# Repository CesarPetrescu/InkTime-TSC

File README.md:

# InkTime Smartwatch

**Student:** Cesar Petrescu  
**Group:** 334CD  
**Course:** Testarea Sistemelor de Calcul - Proiect 2026

## Project Overview

This repository contains the complete hardware design for the InkTime smartwatch project.

The watch is built around the Nordic nRF52840 and combines BLE connectivity, an e-paper display, IMU-based motion sensing, USB-C charging, a fuel gauge, a haptic motor driver, and a buck-boost power stage that generates a stable 3.3 V rail from the battery / charger system rail.

## Block Diagram

## Renders and Mechanical Integration

## Repository Outputs

| Directory | File | Purpose |
|---|---|---|
| `Hardware` | `project-tsc.sch` | Fusion 360 / EAGLE schematic source |
| `Hardware` | `project-tsc.brd` | Fusion 360 / EAGLE PCB source |
| `Hardware` | `schema.pdf` | Schematic print-out for review |
| `Manufacturing` | `gerbers.zip` | Gerber manufacturing archive |
| `Manufacturing` | `InkTime.bom` | Assembly Bill of Materials exported from the board |
| `Manufacturing` | `project-tsc.cpl` | Pick and Place / component placement file |
| `Mechanical` | `Exploded.step` | Complete device STEP model in exploded view |
| `Mechanical` | `Closed.step` | Complete device STEP model in closed/assembled view |

## Design BOM Summary

The assembly-ready BOM exported from the board is included in `Manufacturing/InkTime.bom`. The table below repeats the relevant manufacturing data from that file so the design can be reviewed directly from this README.

### Main fitted parts

| Ref | MPN / Value | Qty | Package / footprint | LCSC / procurement | Function | Datasheet / reference |
|---|---|---:|---|---|---|---|
| U1 | NRF52840-QIAA-R | 1 | AQFN50P700X700X85 HS-74N | [C190794](https://www.lcsc.com/product-detail/C190794.html) | Main MCU, BLE radio, USB device | [Nordic product specification](https://docs-be.nordicsemi.com/bundle/nRF52840_PS_v1.8/raw/resource/enus/nRF52840_PS_v1.8.pdf) |
| IC1 | BQ25180YBGR | 1 | BGA8C40P2X4 100X155X50 | [C3682423](https://www.lcsc.com/product-detail/C3682423.html) | Li-ion charger, power path, ship mode | [TI datasheet](https://www.ti.com/lit/ds/symlink/bq25180.pdf) |
| IC9 | RT6160AWSC | 1 | BGA15C40P3X5 140X230X60 | [C7065276](https://www.lcsc.com/product-detail/C7065276.html) | 3 A buck-boost regulator for 3V3 | [Richtek datasheet](https://www.richtek.com/assets/product_file/RT6160A/DS6160A-05.pdf) |
| U2 | MAX17048G+T10 | 1 | SON50P200X200X80-9N | [C89903](https://www.lcsc.com/product-detail/C89903.html) | Battery fuel gauge | [Analog Devices datasheet](https://www.analog.com/media/en/technical-documentation/data-sheets/max17048-max17049.pdf) |
| IC3 | BMA421 | 1 | BMA423 / LGA-12 | [C5242966](https://www.lcsc.com/product-detail/C5242966.html) | Low-power accelerometer / step counter | [Bosch datasheet](https://www.bosch-sensortec.com/media/boschsensortec/downloads/datasheets/bst-bma421-ds000.pdf) |
| IC2 | DRV2605YZFR | 1 | BGA9C50P3X3 144X144X62 | [C81079](https://www.lcsc.com/product-detail/C81079.html) | Haptic driver for ERM/LRA motor | [TI datasheet](https://www.ti.com/lit/ds/symlink/drv2605.pdf) |
| ANT1 | 2450AT18B100E | 1 | ANTC3216X140N | [C155086](https://www.lcsc.com/product-detail/C155086.html) | 2.4 GHz chip antenna | [Johanson datasheet](https://www.johansontechnology.com/datasheets/2450AT18B100/2450AT18B100.pdf) |
| J4 | KH-TYPE-C-16P | 1 | KINGHELM KH-TYPE-C-16P | [C2765186](https://www.lcsc.com/product-detail/C2765186.html) | USB-C receptacle for VBUS and USB 2.0 data | [JLCPCB part page](https://jlcpcb.com/partdetail/KH-TYPE-C-16P/C2765186) |
| D3 | USBLC6-2SC6Y | 1 | SOT95P280X145-6N | [C7519](https://www.lcsc.com/product-detail/C7519.html) | USB ESD protection | [ST datasheet](https://www.st.com/resource/en/datasheet/usblc6-2.pdf) |
| J2 | 503480-2400 | 1 | 503480-2400 5034802400 | [C132354](https://www.lcsc.com/product-detail/C132354.html) | 24-pin 0.5 mm FPC connector for e-paper | [Molex product page](https://www.molex.com/en-us/products/part-detail/5034802400) |
| J1 | TC2030-IDC | 1 DNP | TC2030IDC | Tag-Connect / DNP footprint | SWD programming and debug footprint | [Mechanical drawing](https://www.digikey.com/en/htmldatasheets/production/2094274/0/0/1/tc2030-idc.html) |
| SW_UP, SW_ENT, SW_DN | EVP-AKE31A | 3 | EVP-AKE31A PAN | [C220990](https://www.lcsc.com/product-detail/C220990.html) | Side tactile buttons | [Panasonic product page](https://industry.panasonic.com/global/en/products/control/switch/light-touch/number/evpake31a) |
| D2, D4, D5 | MBR0530T1G | 3 | SOD3716X135N | [C14156](https://www.lcsc.com/product-detail/C14156.html) | E-paper boost Schottky diodes | [onsemi datasheet](https://www.onsemi.com/pdf/datasheet/mbr0530t1-d.pdf) |
| Q1 | DMG2305UX-7 | 1 | SOT-23 | [C7418](https://www.lcsc.com/product-detail/C7418.html) | P-MOSFET display power gate | [Diodes Inc datasheet](https://www.diodes.com/assets/Datasheets/DMG2305UX.pdf) |
| Q3 | SI1308EDL-T1-GE3 | 1 | SOT-323 | [C146997](https://www.lcsc.com/product-detail/C146997.html) | N-MOSFET display driver switch | [Vishay datasheet](https://www.vishay.com/docs/63399/si1308edl.pdf) |
| X1 | X322532MSB4SI, 32 MHz | 1 | XTAL 2016 N | [C9002](https://www.lcsc.com/product-detail/C9002.html) | Main high-frequency crystal | [LCSC reference](https://www.lcsc.com/product-detail/C9002.html) |
| X2 | X322532768KHZ, 32.768 kHz | 1 | XTAL 3215 N | [C32346](https://www.lcsc.com/product-detail/C32346.html) | Low-frequency RTC crystal | [LCSC reference](https://www.lcsc.com/product-detail/C32346.html) |
| Battery | LP502030, 3.7 V, 250 mAh | 1 | Custom 3D model | [TME product page](https://www.tme.eu/ro/details/accu-lp502030_cl/acumulatori/cellevia-batteries/l502030/) | Main LiPo energy source | [AKYGA LP502030 datasheet](https://www.tme.eu/Document/b9e12bf26ad0ba929a22ab5d58f022cd/AKY0106.pdf) |
| Display | Waveshare 1.54 inch e-paper, 200x200 | 1 | Custom 3D model + J2 FPC | [TME product page](https://www.tme.eu/en/details/wsh-12561/e-paper/waveshare/12561/) | Main user display | [Specification PDF](https://www.tme.eu/Document/0ca57a8ffbcd57b5bca53252eb9d6ec3/WSH-12561.pdf) |
| Motor | FIT0774 | 1 | Custom 3D model / direct wiring | [TME product page](https://www.tme.eu/ro/details/df-fit0774/motoare-dc/dfrobot/fit0774/) | Vibration motor for haptics | [DFRobot product page](https://www.dfrobot.com/product-2297.html) |

### Inductors and passive fitted parts

| Ref | Value / MPN | Qty | Footprint | LCSC / procurement | Notes |
|---|---|---:|---|---|---|
| L1 | LQG15HS3N9S02D, 3.9 nH | 1 | RESC0402 L | [C1581](https://www.lcsc.com/product-detail/C1581.html) | RF matching network |
| L2 | SDFL1005S100KTF, 10 uH | 1 | RESC0402 L | [C1046](https://www.lcsc.com/product-detail/C1046.html) | E-paper power stage |
| L3 | LQG15HS15NJ02D, 15 nH | 1 | RESC0402 L | [C1588](https://www.lcsc.com/product-detail/C1588.html) | RF matching network |
| L5 | 68 uH generic chip inductor | 1 | RESC0402 L | Custom / verify before order | E-paper boost inductor |
| L7 | FTC252012SR47MBCA, 0.47 uH | 1 | INDC2016X100N | [C5832368](https://www.lcsc.com/product-detail/C5832368.html) | RT6160 buck-boost inductor |
| C1-ED-DR | 10 uF, CL05A106MQ5NUNC | 1 | RESC0402 N | [C19702](https://www.lcsc.com/product-detail/C19702.html) | E-paper bulk capacitor |
| C1, C2, C17, C18 | 12 pF, CL03C120JA3NNNC | 4 | RESC0201 L | [C1551](https://www.lcsc.com/product-detail/C1551.html) | Crystal load capacitors |
| C2-EP-DR, C6, C20, C21 | 4.7 uF, CL05A475KQ5NQNC | 4 | RESC0402 N | [C19666](https://www.lcsc.com/product-detail/C19666.html) | Power decoupling / display rail |
| C3, C4 | 1 pF, CL03C010CA3GNNC | 2 | RESC0201 N | [C1546](https://www.lcsc.com/product-detail/C1546.html) | RF matching capacitors |
| C5, C7, C8, C12, C19, C23, C27, C34, C42 | 100 nF / 0.1 uF, CL03A104KA3NNNC | 9 | 0201 variants | [C1525](https://www.lcsc.com/product-detail/C1525.html) | Local decoupling capacitors |
| C9 | 820 pF, CL03B821KO3NNNC | 1 | RESC0201 N | [C3014407](https://www.lcsc.com/product-detail/C3014407.html) | Support capacitor |
| C11 | 100 pF, CL03C101JA3NNNC | 1 | RESC0201 L | [C1555](https://www.lcsc.com/product-detail/C1555.html) | Support capacitor |
| C14, C43 | 4.7 uF, CL03A475KQ3CSNC | 2 | RESC0201 L | [C15850](https://www.lcsc.com/product-detail/C15850.html) | Local bulk capacitors |
| C15 | 1.0 uF, CL03A105KQ3NNNC | 1 | RESC0201 L | [C15849](https://www.lcsc.com/product-detail/C15849.html) | Support capacitor |
| C16 | 47 nF, CL03B473KO3NNNC | 1 | RESC0201 L | [C106094](https://www.lcsc.com/product-detail/C106094.html) | Support capacitor |
| C24, C39 | 10 uF, CL03A106MQ3CSNC | 2 | RESC0201 L | [C19702](https://www.lcsc.com/product-detail/C19702.html) | Power rail capacitors |
| C25, C33 | 22 uF, CL03A226MP3CSNC | 2 | RESC0201 L | [C29777](https://www.lcsc.com/product-detail/C29777.html) | 3V3 bulk capacitors |
| C29, C30, C31, C32, C37, C38 | 1 uF, CL03A105KQ3NNNC | 6 | CAPC0201X13N | [C15849](https://www.lcsc.com/product-detail/C15849.html) | Button debounce / local support |
| EDP_C1, EDP_C2 | 1 uF, CL03A105KQ3NNNC | 2 | RESC0201 L | [C15849](https://www.lcsc.com/product-detail/C15849.html) | E-paper driver capacitors |
| EDP_C5 | 0.1 uF / 50 V, CL03A104KA3NNNC | 1 | RESC0201 L | [C1525](https://www.lcsc.com/product-detail/C1525.html) | E-paper driver capacitor |
| EDP_C6, EDP_C7, EDP_C8, EDP_C9, EDP_C10, EDP_C11, EDP_C12 | 1 uF / 50 V, CL03A105KQ3NNNC | 7 | RESC0201 L | [C15849](https://www.lcsc.com/product-detail/C15849.html) | E-paper charge pump capacitors |
| R1, R2, R3 | 0 ohm, 0201WMJ000XT5E | 3 | 0201 | [C17168](https://www.lcsc.com/product-detail/C17168.html) | Configuration / strap resistors |
| R1_EP_DR1 | 0.47 ohm, 0201WMF4700TCE | 1 | 0201 | [C222406](https://www.lcsc.com/product-detail/C222406.html) | Display driver current path |
| R1_USB, R2_USB | 5.1 k, 0201WMF5101TCE | 2 | 0201 | [C25905](https://www.lcsc.com/product-detail/C25905.html) | USB-C CC pull-down resistors |
| R2_EP_DR, R5, R7, R8, R9, R_PWR_EPD | 10 k, 0201WMF1002TCE | 6 | 0201 | [C25804](https://www.lcsc.com/product-detail/C25804.html) | Pull resistors / display control |
| R17, R18 | 3.3 k, 0201WMF3301TCE | 2 | 0201 | [C25890](https://www.lcsc.com/product-detail/C25890.html) | I2C pull-up resistors |
| R_TYPE_SEL | 2.2 ohm, 0201WMJ0220TCE | 1 | 0201 | [C31998](https://www.lcsc.com/product-detail/C31998.html) | Haptic driver type select |

### DNP / not assembled

| Ref | Quantity | Purpose |
|---|---:|---|
| SJ1 | 1 | Solder jumper / programming footprint |
| TP_3V3, TP_3V3_2, TP_BAT_GND, TP_GND, TP_ON, TP_OP, TP_RESET, TP_SCL, TP_SDA, TP_SWDCLK, TP_SWDIO, TP_SWO, TP_VBAT, TP_VREG | 14 | Test pads, no component assembled |
| C10, C13, C22 | 3 | Not connected / tuning DNP capacitors |
| J1 | 1 | TC2030-IDC debug footprint, not assembled as a normal connector |

### Passives and support parts

- All resistors in the assembly BOM use 0201 footprints.
- The passive packages, values, quantities, and LCSC order codes are listed explicitly in the table above.
- Test pads and debug-only assembly aids are marked as DNP so they are visible during review but not placed as fitted components.

## Hardware Architecture and Functionality

### 1. MCU and RF subsystem

The central controller is the **nRF52840**. It provides:

- ARM Cortex-M4F running at 64 MHz
- BLE radio in the 2.4 GHz ISM band
- full-speed USB device support
- SPI, I2C, GPIO, ADC, and SWD interfaces
- enough Flash and RAM for the smartwatch firmware stack

The RF feed uses the nRF52840 ANT pin, a discrete matching network, and the Johanson **2450AT18B100E** chip antenna.

The antenna section follows the project constraints:

- antenna placed toward the PCB edge
- no routing below the antenna
- no GND pour below the antenna

Clocking is split between:

- **X1 32 MHz** for the main system
- **X2 32.768 kHz** for RTC and low-power timing

### 2. Power path

The power tree is:

`USB-C VBUS -> BQ25180 charger / power-path -> VREG -> RT6160 buck-boost -> 3V3 rail`

Battery monitoring is handled in parallel by the MAX17048 fuel gauge.

#### Charger

**IC1 BQ25180YBGR** receives VBUS from USB-C and manages battery charging, ship mode, and the regulated system path. Its interrupt line is exposed to the MCU as `PMIC_INT`.

#### Buck-boost regulator

**IC9 RT6160AWSC** converts the system rail to a stable 3.3 V output used by the MCU and peripherals. The design uses L7 and the required input and output capacitors from the reference schematic.

#### Fuel gauge

**U2 MAX17048G+T10** monitors the battery and exposes an alert output to the MCU. This gives the firmware a direct low-battery interrupt path.

### 3. Display subsystem

The display is a **1.54 inch 200x200 Waveshare e-paper panel** connected through **J2**, a 24-pin 0.5 mm FPC connector.

Interface signals:

- SPI clock: `SCK`
- SPI data: `MOSI`
- Chip select: `EPD_CS`
- Control GPIOs: `EPD_DC`, `EPD_RST`, `EPD_BUSY`

### 4. Motion sensing

**IC3 BMA421** is the accelerometer used for motion sensing, step counting, and interrupt-driven wake-up.

It is connected on the shared I2C bus and exposes two interrupt pins:

- `IMU_INT1`
- `IMU_INT2`

This lets the firmware wake the system on motion-related events without polling continuously.

### 5. Haptic feedback

**IC2 DRV2605YZFR** drives the **FIT0774** vibration motor.

It is controlled over I2C and uses an enable signal from the MCU. The output nodes are also broken out to test pads, which simplifies debugging and rework.

### 6. USB-C and ESD protection

**J4** is the USB-C connector used for power input and USB data.

- `VBUS` feeds the charger input
- `D+` and `D-` go to the nRF52840 USB interface
- `R1_USB` and `R2_USB` are 5.1 k pull-down resistors on the CC pins
- `D3 USBLC6-2SC6Y` protects the USB lines against ESD events

### 7. Debug and bring-up

**J1 TC2030-IDC** provides the SWD programming and debug interface.

The following debug / bring-up signals are also available on dedicated test pads:

- `TP_3V3`
- `TP_3V3_2`
- `TP_VREG`
- `TP_VBAT`
- `TP_BAT_GND`
- `TP_GND`
- `TP_SDA`
- `TP_SCL`
- `TP_SWDIO`
- `TP_SWDCLK`
- `TP_SWO`
- `TP_RESET`
- `TP_OP`
- `TP_ON`

### 8. User interface

The watch uses three side buttons:

- `SW_UP`
- `SW_ENT`
- `SW_DN`

Each button is connected to a GPIO input and paired with a pull resistor and a 1 uF capacitor for debounce.

## nRF52840 Pin Usage

| nRF pin | Signal | Connected block | Reason |
|---|---|---|---|
| P0.00 / XL1 | XL1 | X2 32.768 kHz crystal | RTC clock input |
| P0.01 / XL2 | XL2 | X2 32.768 kHz crystal | RTC clock output |
| XC1 / XC2 | XC1 / XC2 | X1 32 MHz crystal | Main HF clock for MCU and radio |
| P0.02 | SCK | E-paper connector J2 | SPI clock for display |
| P0.03 | MOSI | E-paper connector J2 | SPI data for display |
| P0.05 | EPD_CS | E-paper connector J2 | Display chip select |
| P0.06 | SDA | IC1, IC2, IC3, U2, IC9 through links | Shared I2C data |
| P0.07 | SCL | IC1, IC2, IC3, U2, IC9 through links | Shared I2C clock |
| P0.08 | IMU_INT1 | BMA421 | Motion / wake interrupt |
| P0.10 | ALERT | MAX17048 | Battery alert interrupt |
| P0.11 | PMIC_INT | BQ25180 | Charger / power-path interrupt |
| P0.12 | HAPTIC_EN | DRV2605 | Enables haptic driver |
| P0.13 | SW_UP | User button | Navigation input |
| P0.14 | SW_ENT | User button | Confirm / enter input |
| P0.15 | EPD_DC | E-paper connector J2 | Display data / command select |
| P0.16 | EPD_RST | E-paper connector J2 | Display reset |
| P0.17 | EPD_BUSY | E-paper connector J2 | Display busy indication |
| P0.18 / RESET | RESET | SWD header J1 and TP_RESET | Hardware reset |
| P1.00 | SWO | SWD header J1 and TP_SWO | Debug trace output |
| P1.01 | P1.01 / EPD_GATE | Q1 gate control | Power gates the display rail |
| P1.02 | SW_DN | User button | Navigation input |
| P1.08 | IMU_INT2 | BMA421 | Secondary motion / gesture interrupt |
| D+ / D- | USB D+ / D- | D3 and J4 | USB data |
| VBUS | VBUS detect | J4 / charger path | USB power sense |
| ANT | RF output | Matching network and ANT1 | BLE antenna feed |
| SWDIO | SWDIO | J1 and TP_SWDIO | SWD data |
| SWDCLK | SWDCLK | J1 and TP_SWDCLK | SWD clock |

## Power Budget and Battery-Life Estimation

The selected battery is the **LP502030 LiPo, 3.7 V / 250 mAh**. The estimate below uses typical planning currents from the component datasheets and an assumed light smartwatch workload. Final current must be measured on physical hardware because BLE interval, display refresh rate, haptic usage, firmware sleep state, and DC/DC efficiency dominate the result.

Assumed daily usage profile:

- BLE advertising / light connection duty cycle active through the day
- BMA421 left in low-power interrupt mode
- e-paper refreshed 12 times per hour, 2 s per refresh
- haptic motor used 20 times per day, 200 ms per event
- display rail switched off by Q1 between refreshes
- 20% system margin added for regulator loss, leakage, firmware overhead, and component tolerance

| Block / mode | Typical current while active | Duty cycle assumption | Average current contribution |
|---|---:|---:|---:|
| nRF52840 sleep + RTC base | 0.003 mA | Always on | 0.003 mA |
| nRF52840 BLE radio events | 5.0 mA during TX/RX bursts | Low-duty BLE average | 0.080 mA |
| BMA421 accelerometer | 0.014 mA | Low-power motion detect | 0.014 mA |
| MAX17048 fuel gauge | 0.023 mA | Always on | 0.023 mA |
| BQ25180 charger / power-path leakage | 0.001 mA | Battery mode | 0.001 mA |
| RT6160 buck-boost quiescent and light-load loss | 0.006 mA | Always on | 0.006 mA |
| E-paper standby with rail gated | 0.001 mA | Between refreshes | 0.001 mA |
| E-paper refresh | 8.0 mA | 2 s x 12 refreshes / hour | 0.053 mA |
| DRV2605 + FIT0774 haptic event | 80 mA | 20 x 0.2 s / day | 0.004 mA |
| Buttons and static GPIOs | ~0 mA | No button held | ~0 mA |
| Estimated subtotal |  |  | **0.185 mA** |
| 20% design margin |  |  | **0.037 mA** |
| Estimated average current |  |  | **0.222 mA** |

Battery-life estimate:

`Battery life [hours] = battery capacity [mAh] / average current [mA]`

`250 mAh / 0.222 mA = 1126 h = 46.9 days`

Scenario comparison:

| Scenario | Average current | Estimated life | Approximate duration |
|---|---:|---:|---:|
| Light use, interrupt-driven firmware | 0.222 mA | 1126 h | ~46.9 days |
| More frequent BLE/display updates | 0.5 mA | 500 h | ~20.8 days |
| Heavy use / development firmware | 1.0 mA | 250 h | ~10.4 days |
| Mostly active peripherals | 2.0 mA | 125 h | ~5.2 days |

Low-power decisions used in this design:

- the e-paper rail is gated through Q1, so the display does not remain fully powered between refreshes
- the BMA421 can wake the MCU through `IMU_INT1` / `IMU_INT2`, avoiding continuous polling
- the MAX17048 `ALERT` line gives a low-battery interrupt path
- the 32.768 kHz crystal allows accurate RTC timing in low-power modes
- the haptic motor is event-based and has a very small daily average current despite high instantaneous current

## Validation Notes

The board was routed against the project constraints and JLCPCB manufacturing limits:

- PCB stack target: 4 layers with component placement only on Top
- board thickness target: 1.0 mm, matching the project mechanical requirement
- power rails such as `VBUS`, `VREG`, `VBAT`, `3V3`, and `EPD_3V3` routed with 0.3 mm target width where there is enough clearance
- BGA escape and dense IC breakouts use narrower local segments only where required by package geometry
- signal traces use at least 0.15 mm width
- no intentional right-angle routing
- GND copper present on Top and Bottom, with an internal GND reference plane
- via stitching used between GND regions, especially around the nRF52840 RF section
- antenna placed at the outside PCB edge, with no copper pour or signal routing under the antenna keepout
- decoupling capacitors placed next to the supply pins of the MCU, PMIC, regulator, IMU, fuel gauge, haptic driver, and display power stage
- silkscreen is kept to readable component names and clear test-pad labels

ERC / DRC review notes:

- The course-permitted ERC warning `Only INPUT pins on NET ID` is acceptable.
- Dimension warnings caused by the side buttons and USB-C connector are acceptable when caused by mechanical alignment with the case.
- The final manufacturing archive is exported as `Manufacturing/gerbers.zip`.
- The final BOM and Pick and Place files are `Manufacturing/InkTime.bom` and `Manufacturing/project-tsc.cpl`.

### Target PCB rules

- 4-layer PCB (Top, Inner 1, Inner 2, Bottom)
- all components placed on the **Top** layer
- routing allowed on **Top**, **Inner 2**, and **Bottom**
- **Inner 1** is a dedicated GND plane
- GND pour also present on **Top** and **Bottom**
- PCB thickness set to **1.0 mm**
- power traces targeted at **0.3 mm**
- signal traces targeted at **0.15 mm minimum**
- no right-angle tracks
- no copper and no routing below the antenna
- via stitching to the inner GND plane, especially around the RF area

### Placement strategy

The placement follows the course board-shape reference and groups components around the main ICs:

- U1 and the RF matching network near the antenna edge
- IC1, U2, and J4 grouped in the USB / charging area
- IC9, L7, and bulk caps grouped as the 3.3 V power stage
- J2 and the E-paper boost parts grouped together
- IC3 placed close to the MCU while staying away from the antenna keepout area
- IC2 placed close to the haptic output pads and motor connection path

## Design Log

- Started from the course-provided InkTime schematic and mechanical outline.
- Initially targeted a 2-layer stack, but pivoted to a 4-layer stack because routing was significantly easier and required fewer vias thanks to the additional routing layers and the dedicated inner GND plane.
- Grouped the major components by subsystem to make routing, review, and mechanical integration easier.

## References
- Reference schematic: <https://ocw.cs.pub.ro/courses/_media/tsc/inktime_schematic.pdf>
- nRF52840 product page: <https://www.nordicsemi.com/Products/nRF52840>
- BQ25180 product page: <https://www.ti.com/product/BQ25180>
- DRV2605 product page: <https://www.ti.com/product/DRV2605>
- MAX17048 product page: <https://www.analog.com/en/products/max17048.html>
- EVPAKE31A product page: <https://industry.panasonic.com/global/en/products/control/switch/light-touch/number/evpake31a>

## License

This repository uses the license defined in the root `LICENSE` file.

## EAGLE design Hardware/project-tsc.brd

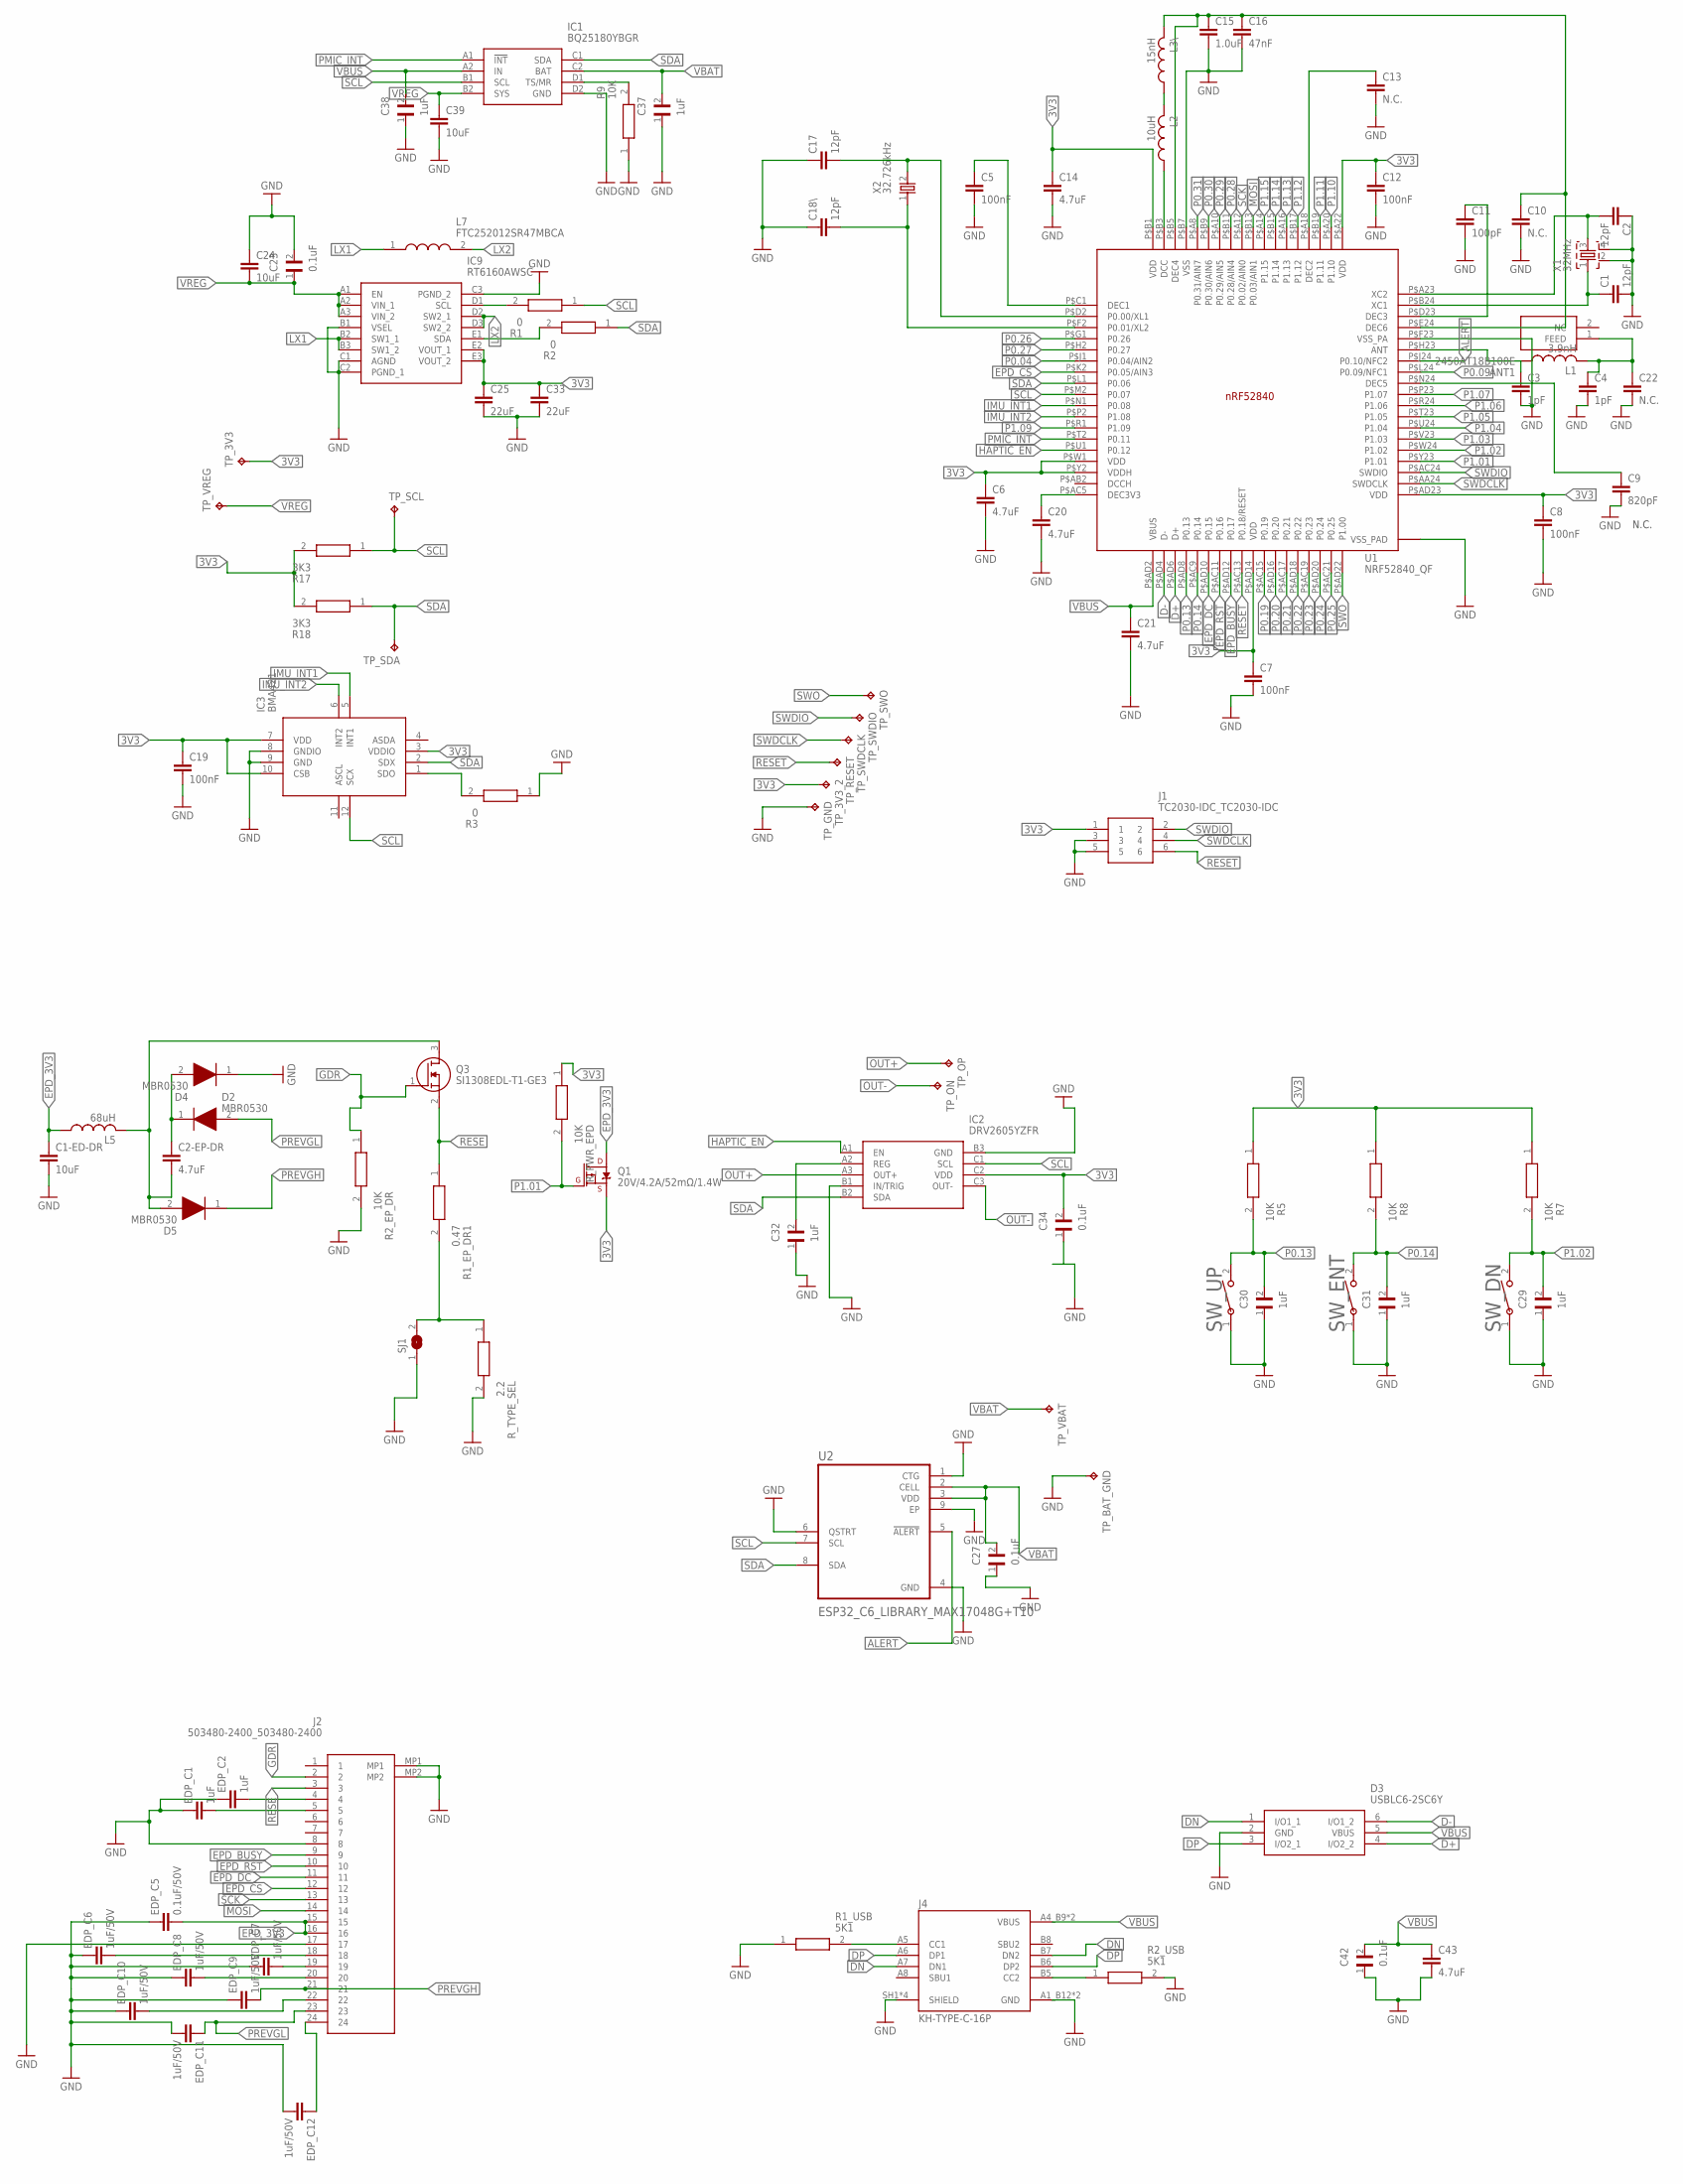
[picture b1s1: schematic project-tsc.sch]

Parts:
ANT1: 2450AT18B100E; 2450AT18B100E_ANTC3216X140N
C1, C2, C17, C18\: 12pF; NORDIC_NRF_3_RESC0201_L
C1-ED-DR: 10uF; NORDIC_NRF_3_RESC0402_N
C2-EP-DR, C6, C20, C21: 4.7uF; NORDIC_NRF_3_RESC0402_N
C3, C4: 1pF; NORDIC_NRF_3_RESC0201_N
C5, C12, C19: 100nF; NORDIC_NRF_3_RESC0201_L
C7, C8: 100nF; NORDIC_NRF_3_RESC0201_N
C9: 820pF; NORDIC_NRF_3_RESC0201_N
C10, C13: N.C.; NORDIC_NRF_3_RESC0201_L
C11: 100pF; NORDIC_NRF_3_RESC0201_L
C14, C43: 4.7uF; NORDIC_NRF_3_RESC0201_L
C15: 1.0uF; NORDIC_NRF_3_RESC0201_L
C16: 47nF; NORDIC_NRF_3_RESC0201_L
C22: N.C.; NORDIC_NRF_3_RESC0201_N
C23, C27, C34, C42: 0.1uF; GRM011R60J152KE01L_2_CAPC0201X13N
C24, C39: 10uF; NORDIC_NRF_3_RESC0201_L
C25, C33: 22uF; NORDIC_NRF_3_RESC0201_L
C29, C30, C31, C32, C37, C38: 1uF; GRM011R60J152KE01L_2_CAPC0201X13N
D2, D4, D5: MBR0530; ESP32_C6_LIBRARY_5_SOD3716X135N
D3: USBLC6-2SC6Y; ESP32_C6_LIBRARY_3_SOT95P280X145-6N
EDP_C1, EDP_C2: 1uF; NORDIC_NRF_3_RESC0201_L
EDP_C5: 0.1uF/50V; NORDIC_NRF_3_RESC0201_L
EDP_C6, EDP_C7, EDP_C8, EDP_C9, EDP_C10, EDP_C11, EDP_C12: 1uF/50V; NORDIC_NRF_3_RESC0201_L
IC1: BQ25180YBGR; BQ25180YBGR_BGA8C40P2X4_100X155X50
IC2: DRV2605YZFR; DRV2605YZFR_BGA9C50P3X3_144X144X62
IC3: BMA421; BMA423_BMA423
IC9: RT6160AWSC; RT6160AWSC_BGA15C40P3X5_140X230X60
J1: TC2030-IDC_TC2030-IDC; TC2030-IDC_TC2030IDC
J2: 503480-2400_503480-2400; 503480-2400_5034802400
J4: KH-TYPE-C-16P; KH-TYPE-C-16P_KINGHELM_KH-TYPE-C-16P
L1: 3.9nH; NORDIC_NRF_2_RESC0402_L
L2: 10uH; NORDIC_NRF_2_RESC0402_L
L3\: 15nH; NORDIC_NRF_2_RESC0402_L
L5: 68uH; NORDIC_NRF_2_RESC0402_L
L7: FTC252012SR47MBCA; MLP2016SR47MT0S1_INDC2016X100N
Q1: 20V/4.2A/52mΩ/1.4W; ESP32_C6_LIBRARY_4_ESP32_C6_LIBRARY_4_ESP32_C6_LIBRARY_4_ES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
Q3: SI1308EDL-T1-GE3; ESP32_C6_LIBRARY_6_SOT65P210X110-3N
R1, R2, R3: 0; CPF0201D7K68C1_0201
R1_EP_DR1: 0.47; CPF0201D7K68C1_0201
R1_USB, R2_USB: 5K1; CPF0201D7K68C1_0201
R2_EP_DR, R5, R7, R8, R9: 10K; CPF0201D7K68C1_0201
R17, R18: 3K3; CPF0201D7K68C1_0201
R_PWR_EPD: 10K; CPF0201D7K68C1_0201
R_TYPE_SEL: 2.2; CPF0201D7K68C1_0201
SJ1: ESP32_C6_LIBRARY_7_JUMPER_SJ
SW_DN: 2025-10-22_07-23-44_LIBRARY_EVP-AKE31ASW_EVP-AKE3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; 2025-10-22_07-23-44_LIBRARY_SW_EVP-AKE31A_PAN
SW_ENT: 2025-10-22_07-23-44_LIBRARY_EVP-AKE31ASW_EVP-AKE3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; 2025-10-22_07-23-44_LIBRARY_SW_EVP-AKE31A_PAN
SW_UP: 2025-10-22_07-23-44_LIBRARY_EVP-AKE31ASW_EVP-AKE3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; 2025-10-22_07-23-44_LIBRARY_SW_EVP-AKE31A_PAN
TP_3V3, TP_3V3_2: HECTOR_WATCH_1_TPTP20R; HECTOR_WATCH_1_TP20R
TP_BAT_GND: HECTOR_WATCH_1_TPTP20R; HECTOR_WATCH_1_TP20R
TP_GND: HECTOR_WATCH_1_TPTP20R; HECTOR_WATCH_1_TP20R
TP_ON: HECTOR_WATCH_1_TPTP20R; HECTOR_WATCH_1_TP20R
TP_OP: HECTOR_WATCH_1_TPTP20R; HECTOR_WATCH_1_TP20R
TP_RESET: HECTOR_WATCH_1_TPTP20R; HECTOR_WATCH_1_TP20R
TP_SCL: HECTOR_WATCH_1_TPTP20R; HECTOR_WATCH_1_TP20R
TP_SDA: HECTOR_WATCH_1_TPTP20R; HECTOR_WATCH_1_TP20R
TP_SWDCLK: HECTOR_WATCH_1_TPTP20R; HECTOR_WATCH_1_TP20R
TP_SWDIO: HECTOR_WATCH_1_TPTP20R; HECTOR_WATCH_1_TP20R
TP_SWO: HECTOR_WATCH_1_TPTP20R; HECTOR_WATCH_1_TP20R
TP_VBAT: HECTOR_WATCH_1_TPTP20R; HECTOR_WATCH_1_TP20R
TP_VREG: HECTOR_WATCH_1_TPTP20R; HECTOR_WATCH_1_TP20R
U1: NRF52840_QF; NORDIC_NRF_4_AQFN50P700X700X85_HS-74N
U2: ESP32_C6_LIBRARY_MAX17048G+T10; ESP32_C6_LIBRARY_SON50P200X200X80-9N
X1: 32MHz; NORDIC_NRF_BT-XTAL_2016_N
X2: 32.726kHz; NORDIC_NRF_1_XTAL_3215_N

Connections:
3V1: C5.1, U1.P$C1 (DEC1)
3V3: C6.1, C7.1, C8.1, C12.1, C14.1, C19.1, C25.1, C33.1, C34.2, IC2.C2 (VDD), IC3.3 (VDDIO), IC3.7 (VDD), IC3.10 (CSB), IC9.E2 (VOUT_1), IC9.E3 (VOUT_2), J1.1, Q1.2 (S), R5.1, R7.1, R8.1, R17.2, R18.2, R_PWR_EPD.1, TP_3V3.TP, TP_3V3_2.TP, U1.P$A22 (VDD), U1.P$AD14 (VDD), U1.P$AD23 (VDD), U1.P$B1 (VDD), U1.P$W1 (VDD), U1.P$Y2 (VDDH)
ALERT: U1.P$J24 (P0.10/NFC2), U2.5 (!ALERT)
D+: D3.4 (I/O2_2), U1.P$AD6 (D+)
D-: D3.6 (I/O1_2), U1.P$AD4 (D-)
DN: D3.1 (I/O1_1), J4.A7 (DN1), J4.B7 (DN2)
DP: D3.3 (I/O2_1), J4.A6 (DP1), J4.B6 (DP2)
EPD_3V3: C1-ED-DR.1, EDP_C5.2, J2.15, J2.16, L5.1, Q1.3 (D)
EPD_BUSY: J2.9, U1.P$AD12 (P0.17)
EPD_CS: J2.12, U1.P$K2 (P0.05/AIN3)
EPD_DC: J2.11, U1.P$AD10 (P0.15)
EPD_RST: J2.10, U1.P$AC11 (P0.16)
ESP_3V1: EDP_C6.2, J2.18
ESP_3V2: EDP_C7.2, J2.19
ESP_3V4: EDP_C8.2, J2.20
ESP_3V6: EDP_C10.2, J2.22
GDR: J2.2, Q3.1 (G), R2_EP_DR.1
GND: C1.2, C1-ED-DR.2, C2.1, C3.2, C4.2, C5.2, C6.2, C7.2, C8.2, C9.2, C10.2, C11.2, C12.2, C13.2, C14.2, C15.2, C16.2, C17.1, C18\.1, C19.2, C20.2, C21.2, C22.2, C23.2, C24.1, C25.2, C27.1, C29.1, C30.1, C31.1, C32.1, C33.2, C34.1, C37.1, C38.1, C39.2, C42.1, C43.2, D3.2 (GND), D4.1 (K), EDP_C1.1, EDP_C2.1, EDP_C5.1, EDP_C6.1, EDP_C7.1, EDP_C8.1, EDP_C9.1, EDP_C10.1, EDP_C11.2, EDP_C12.2, IC1.D2 (GND), IC2.B1 (IN/TRIG), IC2.B3 (GND), IC3.8 (GNDIO), IC3.9 (GND), IC9.B1 (VSEL), IC9.C1 (AGND), IC9.C2 (PGND_1), IC9.C3 (PGND_2), J1.3, J1.5, J2.8, J2.17, J2.MP1, J2.MP2, J4.A1_B12 (GND), J4.A12_B1 (GND), J4.SH1 (SHIELD), J4.SH2 (SHIELD), J4.SH3 (SHIELD), J4.SH4 (SHIELD), R1_USB.1, R2_EP_DR.2, R2_USB.2, R3.1, R9.1, R_TYPE_SEL.2, SJ1.1, SW_DN.1, SW_ENT.1, SW_UP.1, TP_BAT_GND.TP, TP_GND.TP, U1.P$74 (VSS_PAD), U1.P$75 (VSS_PAD), U1.P$76 (VSS_PAD), U1.P$77 (VSS_PAD), U1.P$78 (VSS_PAD), U1.P$79 (VSS_PAD), U1.P$80 (VSS_PAD), U1.P$81 (VSS_PAD), U1.P$82 (VSS_PAD), U1.P$83 (VSS_PAD), U1.P$84 (VSS_PAD), U1.P$85 (VSS_PAD), U1.P$86 (VSS_PAD), U1.P$87 (VSS_PAD), U1.P$88 (VSS_PAD), U1.P$89 (VSS_PAD), U1.P$90 (VSS_PAD), U1.P$B7 (VSS), U1.P$F23 (VSS_PA), U2.1 (CTG), U2.4 (GND), U2.6 (QSTRT), U2.9 (EP), X1.2, X1.4
GND1: C17.2, U1.P$D2 (P0.00/XL1), X2.2
GND2: C18\.2, U1.P$F2 (P0.01/XL2), X2.1
GND3: C2.2, U1.P$A23 (XC2), X1.3
HAPTIC_EN: IC2.A1 (EN), U1.P$U1 (P0.12)
IMU_INT1: IC3.5 (INT1), U1.P$N1 (P0.08)
IMU_INT2: IC3.6 (INT2), U1.P$P2 (P1.08)
LX1: IC9.B2 (SW1_1), IC9.B3 (SW1_2), L7.1
LX2: IC9.D2 (SW2_1), IC9.D3 (SW2_2), L7.2
MOSI: J2.14, U1.P$B13 (P0.03/AIN1)
unnamed: L2.1, U1.P$B3 (DCC)
unnamed: L2.2, L3\.1
unnamed: C10.1, C15.1, C16.1, L3\.2, U1.P$B5 (DEC4), U1.P$E24 (DEC6)
unnamed: R1_EP_DR1.2, R_TYPE_SEL.1, SJ1.2
unnamed: IC1.D1 (TS/MR), R9.2
unnamed: C2-EP-DR.2, D5.2 (A), L5.2, Q3.3 (D)
unnamed: C2-EP-DR.1, D2.1 (K), D4.2 (A)
unnamed: J4.A5 (CC1), R1_USB.2
unnamed: J4.B5 (CC2), R2_USB.1
unnamed: EDP_C2.2, J2.4
unnamed: EDP_C1.2, J2.5
unnamed: C32.2, IC2.A2 (REG)
unnamed: C13.1, U1.P$A18 (DEC2)
unnamed: C11.1, U1.P$D23 (DEC3)
unnamed: C1.1, U1.P$B24 (XC1), X1.1
unnamed: IC9.D1 (SCL), R1.2
unnamed: IC9.E1 (SDA), R2.2
unnamed: EDP_C12.1, J2.24
unnamed: IC3.1 (SDO), R3.2
unnamed: C20.1, U1.P$AC5 (DEC3V3)
unnamed: C9.1, U1.P$N24 (DEC5)
unnamed: ANT1.1 (FEED), C4.1, C22.1, L1.2
unnamed: C3.1, L1.1, U1.P$H23 (ANT)
OUT+: IC2.A3 (OUT+), TP_OP.TP
OUT-: IC2.C3 (OUT-), TP_ON.TP
P0.04: U1.P$J1 (P0.04/AIN2)
P0.09: U1.P$L24 (P0.09/NFC1)
P0.13: C30.2, R5.2, SW_UP.2, U1.P$AD8 (P0.13)
P0.14: C31.2, R8.2, SW_ENT.2, U1.P$AC9 (P0.14)
P0.19: U1.P$AC15 (P0.19)
P0.20: U1.P$AD16 (P0.20)
P0.21: U1.P$AC17 (P0.21)
P0.22: U1.P$AD18 (P0.22)
P0.23: U1.P$AC19 (P0.23)
P0.24: U1.P$AD20 (P0.24)
P0.25: U1.P$AC21 (P0.25)
P0.26: U1.P$G1 (P0.26)
P0.27: U1.P$H2 (P0.27)
P0.28: U1.P$B11 (P0.28/AIN4)
P0.29: U1.P$A10 (P0.29/AIN5)
P0.30: U1.P$B9 (P0.30/AIN6)
P0.31: U1.P$A8 (P0.31/AIN7)
P1.01: Q1.1 (G), R_PWR_EPD.2, U1.P$Y23 (P1.01)
P1.02: C29.2, R7.2, SW_DN.2, U1.P$W24 (P1.02)
P1.03: U1.P$V23 (P1.03)
P1.04: U1.P$U24 (P1.04)
P1.05: U1.P$T23 (P1.05)
P1.06: U1.P$R24 (P1.06)
P1.07: U1.P$P23 (P1.07)
P1.09: U1.P$R1 (P1.09)
P1.10: U1.P$A20 (P1.10)
P1.11: U1.P$B19 (P1.11)
P1.12: U1.P$B17 (P1.12)
P1.13: U1.P$A16 (P1.13)
P1.14: U1.P$B15 (P1.14)
P1.15: U1.P$A14 (P1.15)
PMIC_INT: IC1.A1 (!INT), U1.P$T2 (P0.11)
PREVGH: D5.1 (K), EDP_C9.2, J2.21
PREVGL: D2.2 (A), EDP_C11.1, J2.23
RESE: J2.3, Q3.2 (S), R1_EP_DR1.1
RESET: J1.6, TP_RESET.TP, U1.P$AC13 (P0.18/RESET)
SCK: J2.13, U1.P$A12 (P0.02/AIN0)
SCL: IC1.B1 (SCL), IC2.C1 (SCL), IC3.12 (SCX), R1.1, R17.1, TP_SCL.TP, U1.P$M2 (P0.07), U2.7 (SCL)
SDA: IC1.C1 (SDA), IC2.B2 (SDA), IC3.2 (SDX), R2.1, R18.1, TP_SDA.TP, U1.P$L1 (P0.06), U2.8 (SDA)
SWDCLK: J1.4, TP_SWDCLK.TP, U1.P$AA24 (SWDCLK)
SWDIO: J1.2, TP_SWDIO.TP, U1.P$AC24 (SWDIO)
SWO: TP_SWO.TP, U1.P$AD22 (P1.00)
VBAT: C27.2, C37.2, IC1.C2 (BAT), TP_VBAT.TP, U2.2 (CELL), U2.3 (VDD)
VBUS: C21.1, C38.2, C42.2, C43.1, D3.5 (VBUS), IC1.A2 (IN), J4.A4_B9 (VBUS), J4.A9_B4 (VBUS), U1.P$AD2 (VBUS)
VREG: C23.1, C24.2, C39.1, IC1.B2 (SYS), IC9.A1 (EN), IC9.A2 (VIN_1), IC9.A3 (VIN_2), TP_VREG.TP

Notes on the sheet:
N.C.

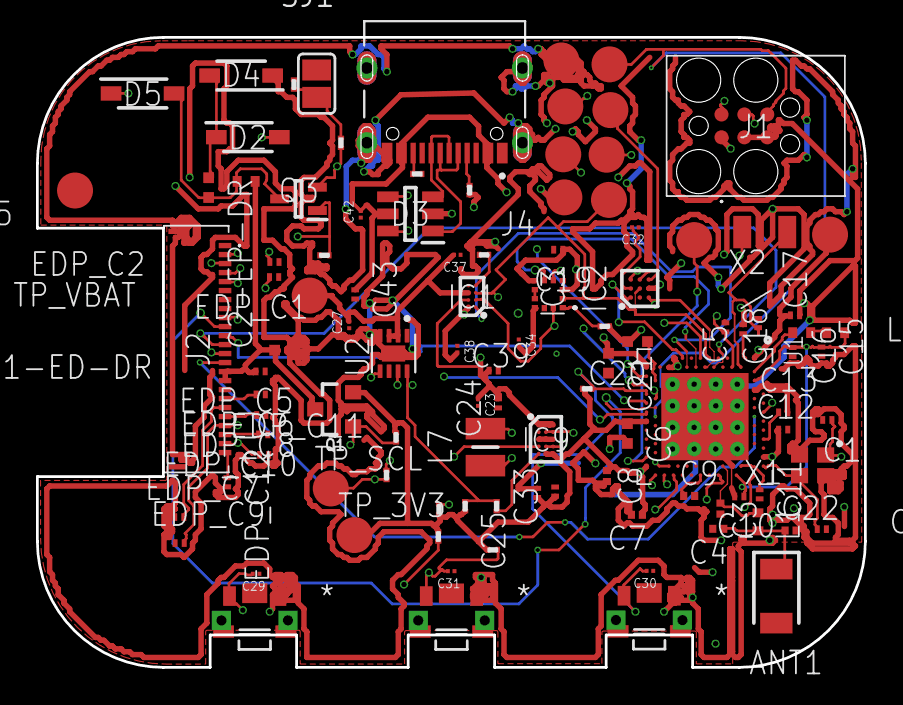
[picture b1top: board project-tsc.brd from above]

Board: 4 copper layers, 46.0 x 35.0 mm, 105 parts (0 on the bottom side), 70 nets.

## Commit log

2026-04-10 # Proiect TSC Cesar Petrescu 334CD
2026-04-10 Fix header formatting in README.md
2026-04-15 Added LICENSE
2026-04-16 Add system block diagram for InkTime Smartwatch in SVG format
    - Created a detailed SVG block diagram illustrating the system architecture of the InkTime Smartwatch.
    - Included components : MCU, E-Paper Display, IMU, Haptic Driver, USB-C, Battery, Fuel Gauge, and Power Management ICs.
    - Added connection lines and labels for various interfaces (SPI, I2C, GPIO) to enhance clarity.
    - Implemented a legend for easy reference to connection types and signal paths.
2026-04-16 remove outdated PCB implementation details
2026-04-19 Refactor code structure for improved readability and maintainability
2026-04-20 Add gerbers.zip file for manufacturing documentation
2026-04-20 Add BOM and project configuration files for manufacturing
2026-04-20 Add new assembly file for project TSC
2026-04-20 Add new STEP files for mechanical components
    - Added Closed.step file (29,966 KB) for closed mechanical assembly.
    - Added Exploded.step file (31,722 KB) for exploded view of mechanical assembly.
2026-04-20 Add detailed assembly BOM and manufacturing files for InkTime project
    - Updated README.md with renders, mechanical integration, and repository outputs.
    - Included a comprehensive design BOM summary with fitted parts, inductors, and passive components.
    - Added a new component placement file (project-tsc.cpl) for manufacturing.
2026-04-20 Update InkTime block diagram SVG and PNG files with improved styling and annotations

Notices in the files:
README.md:
This repository uses the license defined in the root `LICENSE` file.
parts and their libraries:
COPYRIGHT: Copyright (C) 2025 Ultra Librarian. All rights reserved.
